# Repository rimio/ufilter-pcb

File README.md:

# ufilter-pcb

Small PCB for 3rd order LC-ladder Butterworth bandpass filters, using 0603 footprints for capacitors and 0805 footprints for inductors.

Supports end mount SMA connector (Mouser 712-CONSMA020.062-G), PCB mount SMA connector (Mouser  471-SMACONNECTOR) or direct soldering.

 This work is licensed under a [Creative Commons Attribution-ShareAlike 4.0 International License](http://creativecommons.org/licenses/by-sa/4.0/).

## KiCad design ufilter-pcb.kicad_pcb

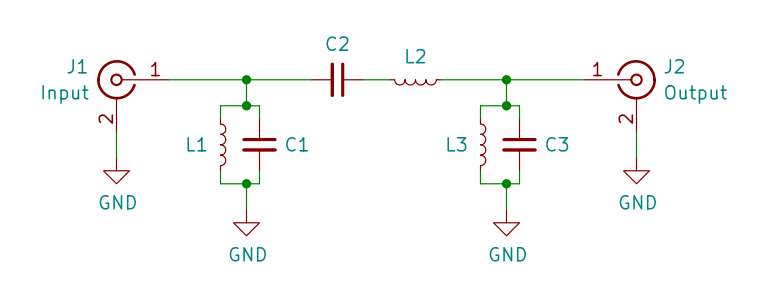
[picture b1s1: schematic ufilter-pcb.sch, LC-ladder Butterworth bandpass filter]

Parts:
C1, C2, C3: C_Small; C_0603_1608Metric_Pad1.08x0.95mm_HandSolder
J1: Input; SMA_Bundled_Edge_PCB
J2: Output; SMA_Bundled_Edge_PCB
L1, L2, L3: L_Small; L_0805_2012Metric_Pad1.15x1.40mm_HandSolder

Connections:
GND: C1.2, C3.2, J1.2 (Ext), J2.2 (Ext), L1.1, L3.1
unnamed: C1.1, C2.2, J1.1 (In), L1.2
unnamed: C2.1, L2.2
unnamed: C3.1, J2.1 (In), L2.1, L3.2

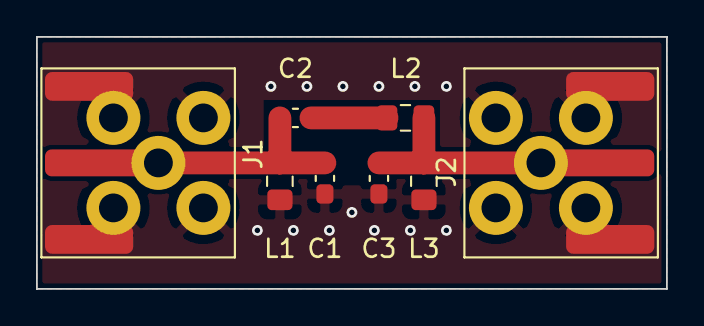
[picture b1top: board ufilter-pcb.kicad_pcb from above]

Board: 2 copper layers, 35.0 x 14.0 mm, 8 parts (0 on the bottom side), 4 nets.

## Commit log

2021-04-06 rev 0
